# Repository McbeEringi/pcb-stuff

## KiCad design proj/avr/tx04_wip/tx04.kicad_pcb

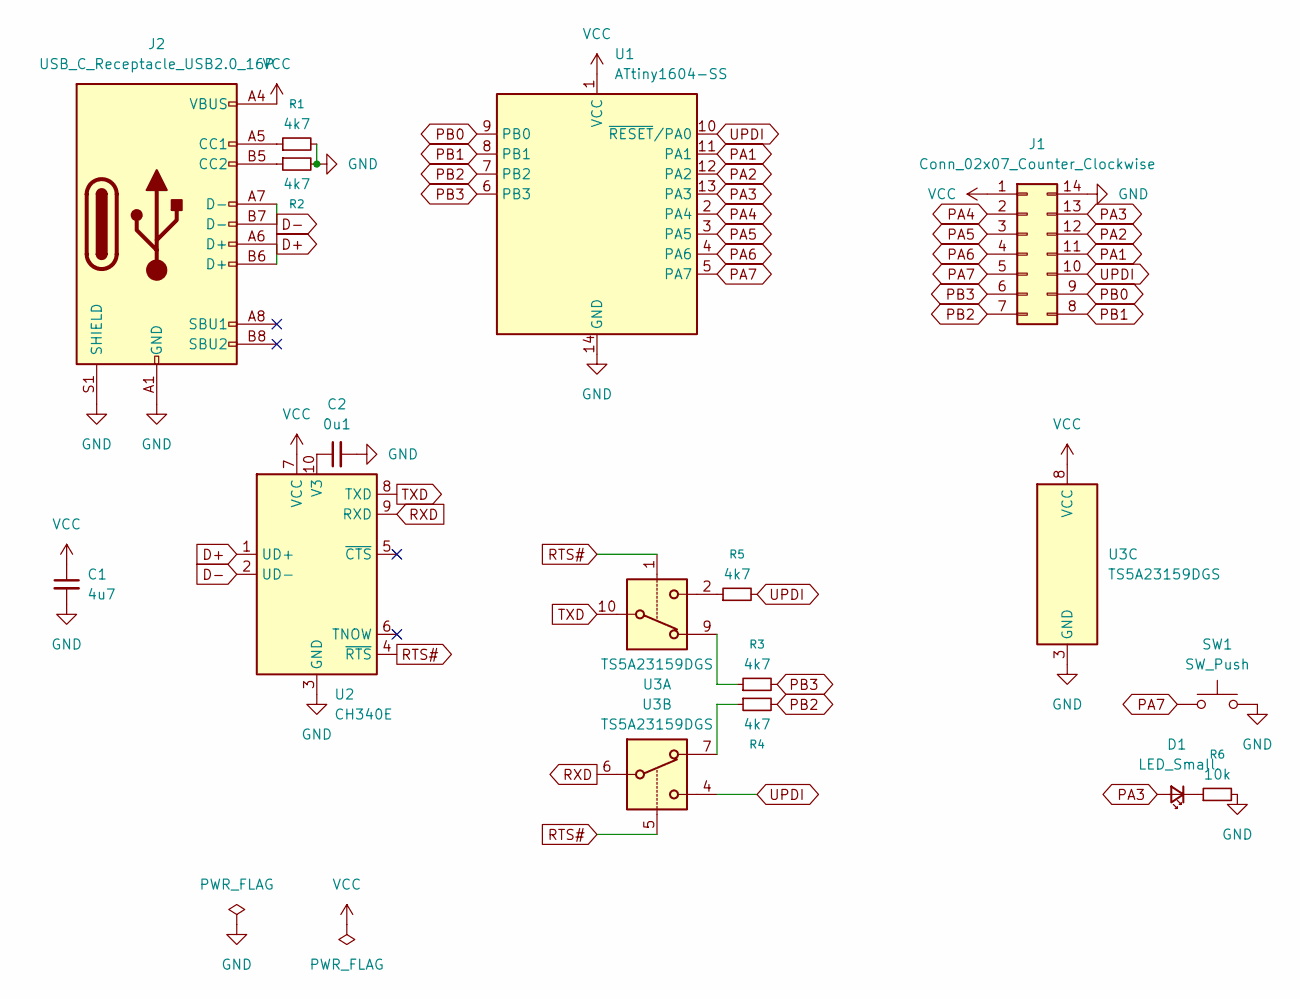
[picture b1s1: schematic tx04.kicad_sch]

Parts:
C1: 4u7; C_0603_1608Metric
C2: 0u1; C_0603_1608Metric
D1: LED_Small; LED_0603_1608Metric
J1: Conn_02x07_Counter_Clockwise; DIP-14_W10.16mm
J2: USB_C_Receptacle_USB2.0_16P; USB_C_Receptacle_GCT_USB4105-xx-A_16P_TopMnt_Horizontal
R1, R2, R3, R4, R5: 4k7; R_0603_1608Metric
R6: 10k; R_0603_1608Metric
SW1: SW_Push; alps-skrp
U1: ATtiny1604-SS; SOIC-14_3.9x8.7mm_P1.27mm
U2: CH340E; MSOP-10_3x3mm_P0.5mm
U3: TS5A23159DGS; VSSOP-10_3x3mm_P0.5mm

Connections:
D+: J2.A6 (D+), J2.B6 (D+), U2.1 (UD+)
D-: J2.A7 (D-), J2.B7 (D-), U2.2 (UD-)
GND: C1.2, C2.2, J1.14, J2.A1 (GND), J2.A12 (GND), J2.B1 (GND), J2.B12 (GND), J2.S1 (SHIELD), R1.2, R2.2, R6.2, SW1.2, U1.14 (GND), U2.3 (GND), U3.3 (GND)
unnamed: D1.1 (K), R6.1
unnamed: J2.A5 (CC1), R1.1
unnamed: J2.B5 (CC2), R2.1
unnamed: R3.1, U3.9
unnamed: R4.1, U3.7
unnamed: R5.1, U3.2
unnamed: C2.1, U2.10 (V3)
PA1: J1.11, U1.11 (PA1)
PA2: J1.12, U1.12 (PA2)
PA3: D1.2 (A), J1.13, U1.13 (PA3)
PA4: J1.2, U1.2 (PA4)
PA5: J1.3, U1.3 (PA5)
PA6: J1.4, U1.4 (PA6)
PA7: J1.5, SW1.1, U1.5 (PA7)
PB0: J1.9, U1.9 (PB0)
PB1: J1.8, U1.8 (PB1)
PB2: J1.7, R4.2, U1.7 (PB2)
PB3: J1.6, R3.2, U1.6 (PB3)
RTS#: U2.4 (~RTS), U3.1, U3.5
RXD: U2.9 (RXD), U3.6
TXD: U2.8 (TXD), U3.10
UPDI: J1.10, R5.2, U1.10 (~RESET/PA0), U3.4
VCC: C1.1, J1.1, J2.A4 (VBUS), J2.A9 (VBUS), J2.B4 (VBUS), J2.B9 (VBUS), U1.1 (VCC), U2.7 (VCC), U3.8 (VCC)

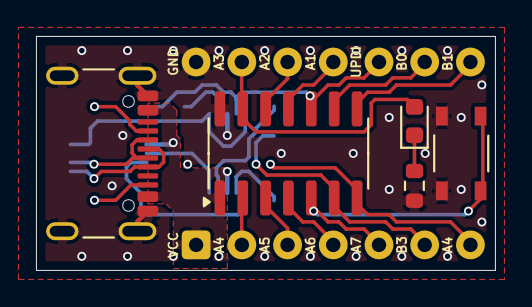
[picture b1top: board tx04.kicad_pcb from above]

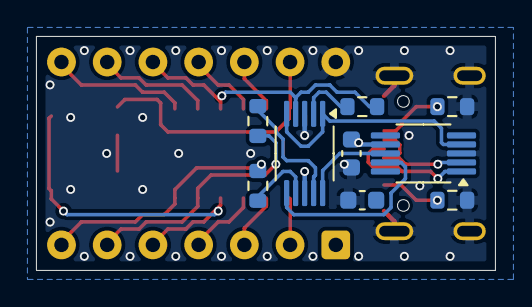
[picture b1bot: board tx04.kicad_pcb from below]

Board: 2 copper layers, 25.5 x 13.0 mm, 15 parts (9 on the bottom side), 26 nets.

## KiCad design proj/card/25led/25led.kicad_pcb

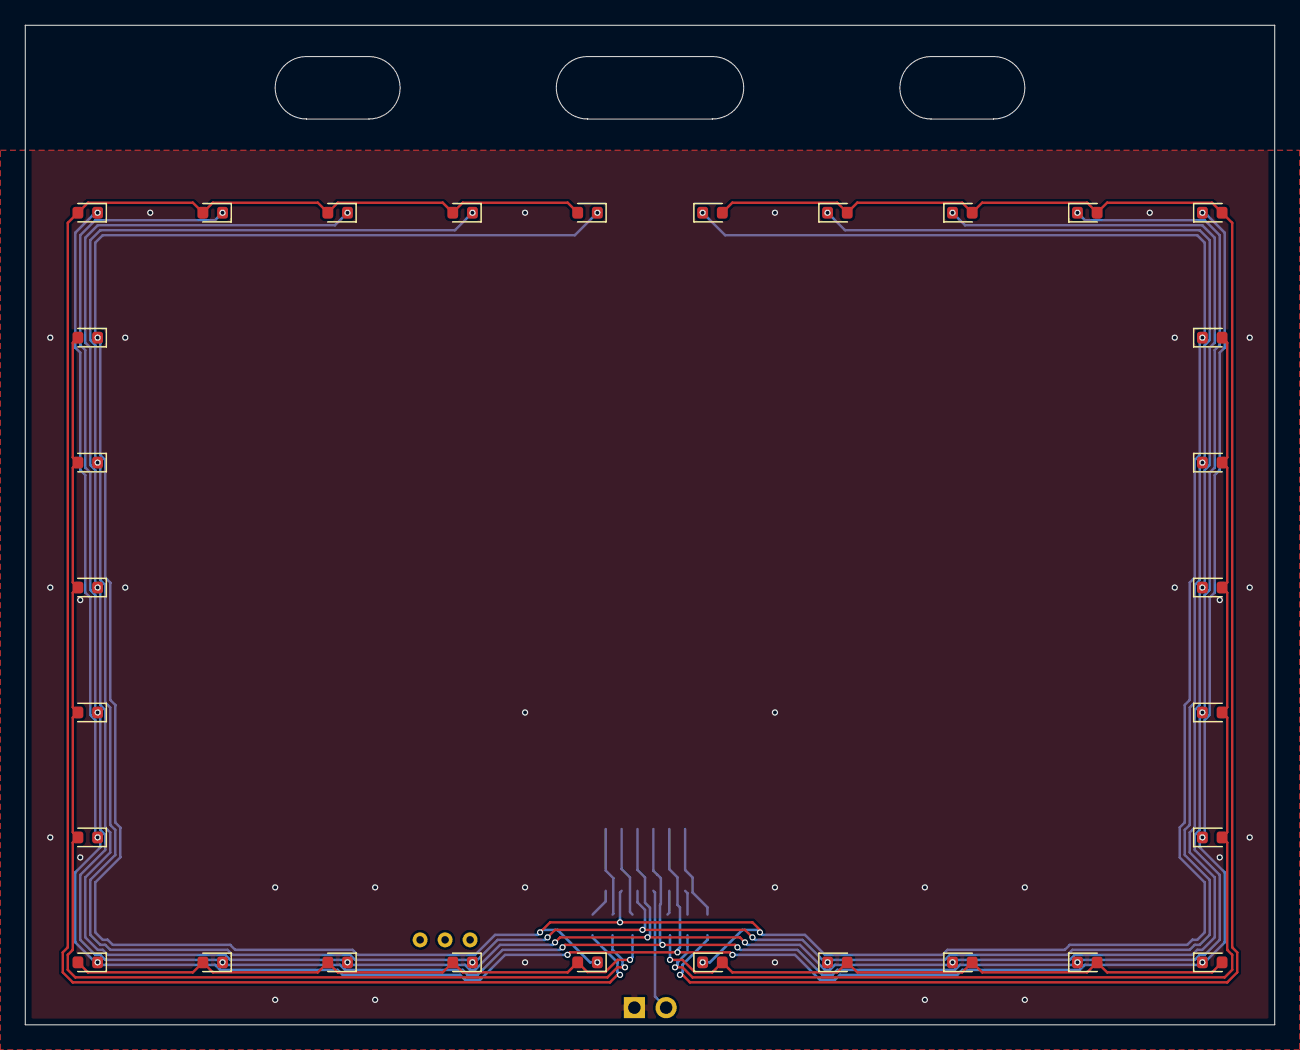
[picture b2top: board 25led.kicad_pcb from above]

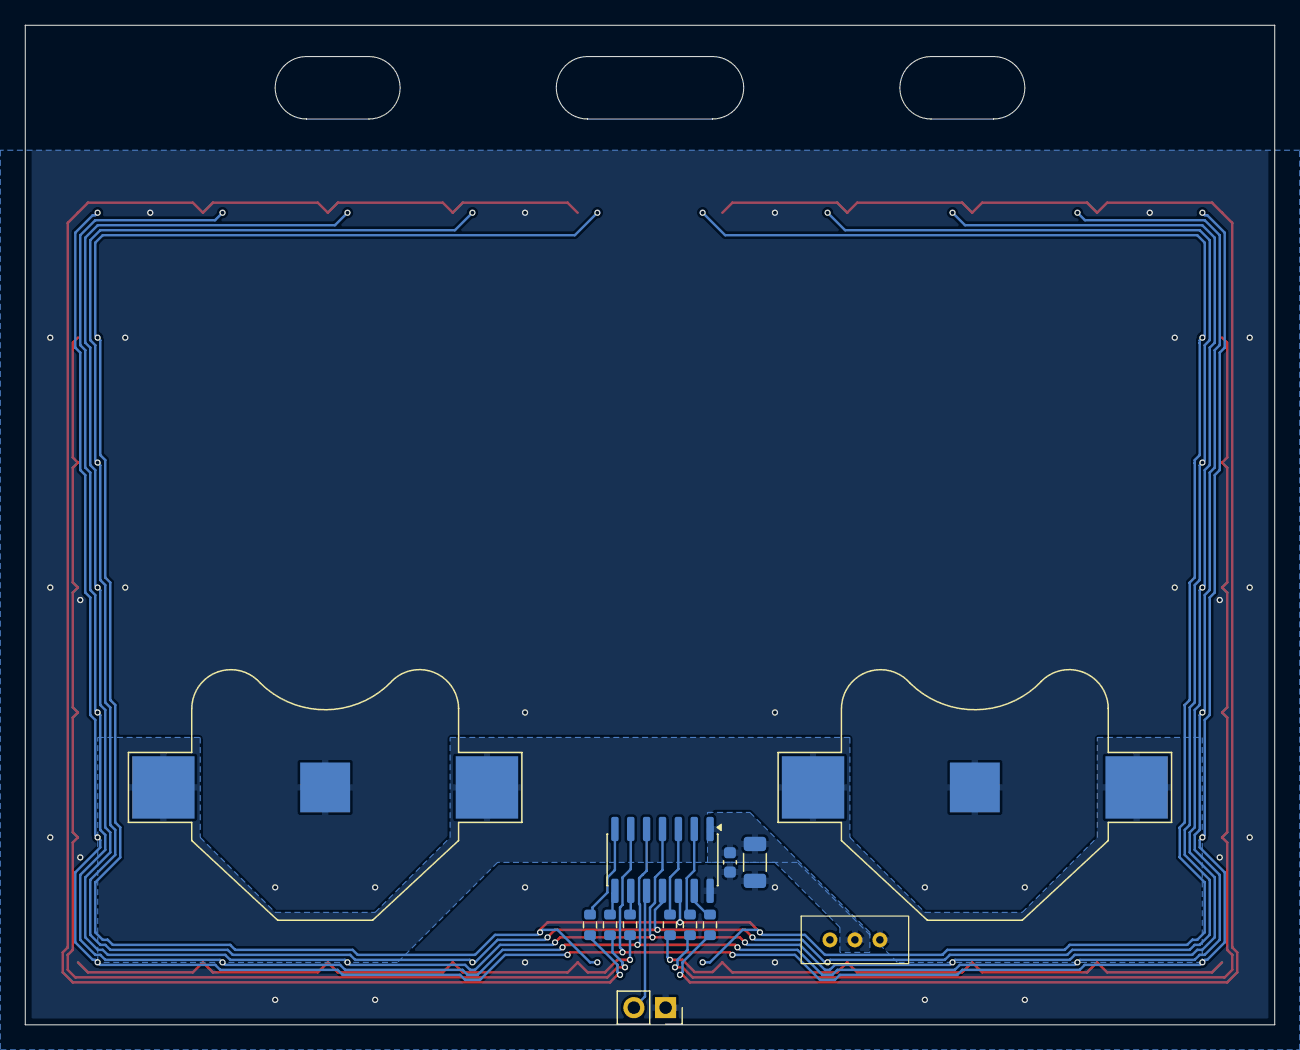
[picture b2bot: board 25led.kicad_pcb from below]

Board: 2 copper layers, 100.0 x 80.0 mm, 43 parts (13 on the bottom side), 21 nets.

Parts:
BT1, BT2: CR2032; BatteryHolder_Multicomp_BC-2001_1x2032
C1: 100u; C_1206_3216Metric
C2: 4u7; C_0603_1608Metric
D1, D2, D3, D4, D5, D6, D7, D8, D9, D10, D11, D12, D13, D14, D15, D16, D17, D18, D19, D20, D21, D22, D23, D24, D25, D26, D27, D28, D29, D30: LED; LED_0603_1608Metric
J1: UPDI; PinSocket_1x02_P2.54mm_Vertical
R1, R2, R3, R4, R5, R6: 100R; R_0603_1608Metric
SW1: SW_SPDT; sw_tht
U1: ATtiny404-SS; SOIC-14_3.9x8.7mm_P1.27mm

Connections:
+BATT: BT1.1 (+), BT2.1 (+), SW1.3 (C)
/_COL1: D1.2 (A), D2.2 (A), D3.2 (A), D4.2 (A), D5.2 (A), R1.2
/_COL2: D6.2 (A), D7.2 (A), D8.2 (A), D9.2 (A), D10.2 (A), R2.2
/_COL3: D11.2 (A), D12.2 (A), D13.2 (A), D14.2 (A), D15.2 (A), R3.2
/_COL4: D16.2 (A), D17.2 (A), D18.2 (A), D19.2 (A), D20.2 (A), R4.2
/_COL5: D21.2 (A), D22.2 (A), D23.2 (A), D24.2 (A), D25.2 (A), R5.2
/_COL6: D26.2 (A), D27.2 (A), D28.2 (A), D29.2 (A), D30.2 (A), R6.2
COL1: R1.1, U1.9 (PB0)
COL2: R2.1, U1.8 (PB1)
COL3: R3.1, U1.7 (PB2)
COL4: R4.1, U1.13 (PA3)
COL5: R5.1, U1.2 (PA4)
COL6: R6.1, U1.3 (PA5)
GND: BT1.2 (-), BT2.2 (-), C1.2, C2.2, J1.1, U1.14 (GND)
ROW1: D1.1 (K), D6.1 (K), D11.1 (K), D16.1 (K), D21.1 (K), D26.1 (K), U1.12 (PA2)
ROW2: D2.1 (K), D7.1 (K), D12.1 (K), D17.1 (K), D22.1 (K), D27.1 (K), U1.11 (PA1)
ROW3: D3.1 (K), D8.1 (K), D13.1 (K), D18.1 (K), D23.1 (K), D28.1 (K), U1.4 (PA6)
ROW4: D4.1 (K), D9.1 (K), D14.1 (K), D19.1 (K), D24.1 (K), D29.1 (K), U1.5 (PA7)
ROW5: D5.1 (K), D10.1 (K), D15.1 (K), D20.1 (K), D25.1 (K), D30.1 (K), U1.6 (PB3)
UPDI: J1.2, U1.10 (~RESET/PA0)
VCC: C1.1, C2.1, SW1.2 (B), U1.1 (VCC)

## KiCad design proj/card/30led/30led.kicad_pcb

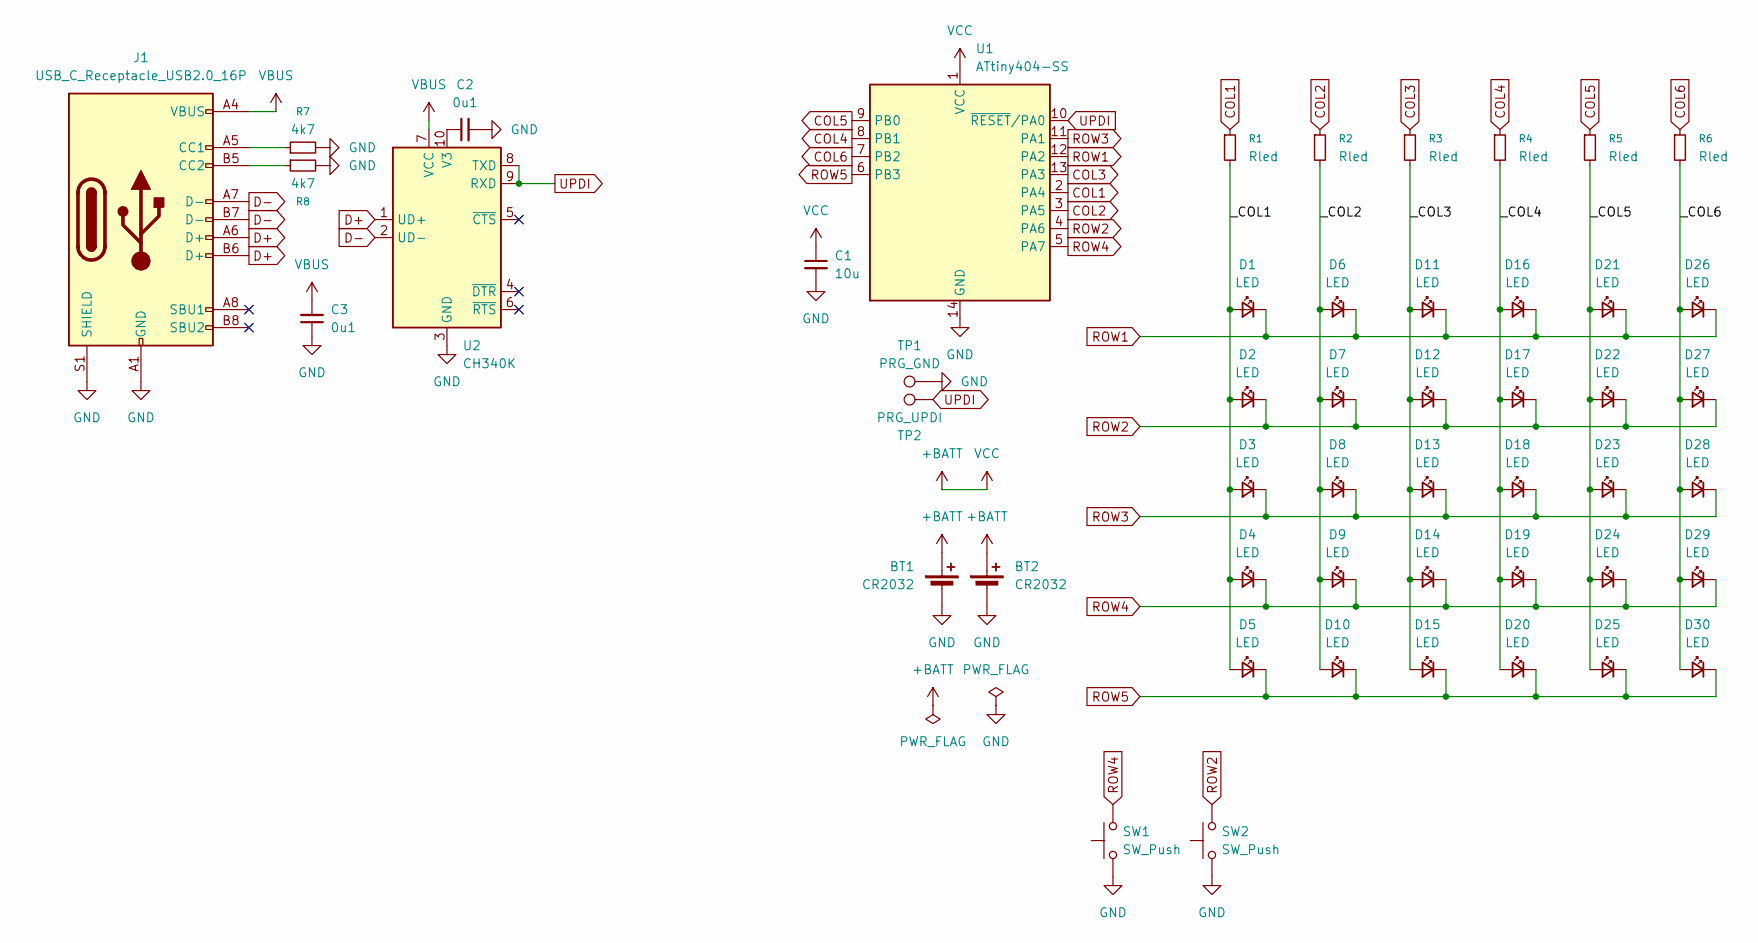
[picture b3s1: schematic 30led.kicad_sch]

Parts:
BT1, BT2: CR2032; BatteryHolder_Multicomp_BC-2001_1x2032
C1: 10u; C_0603_1608Metric
C2, C3: 0u1; C_0603_1608Metric
D1, D2, D3, D4, D5, D6, D7, D8, D9, D10, D11, D12, D13, D14, D15, D16, D17, D18, D19, D20, D21, D22, D23, D24, D25, D26, D27, D28, D29, D30: LED; LED_0603_1608Metric
J1: USB_C_Receptacle_USB2.0_16P; USB_C_Receptacle_GCT_USB4110
R1, R2, R3, R4, R5, R6: Rled; R_0603_1608Metric
R7, R8: 4k7; R_0603_1608Metric
SW1, SW2: SW_Push; alps-skrp
TP1: PRG_GND; TestPoint_Pad_1.5x1.5mm
TP2: PRG_UPDI; TestPoint_Pad_D1.5mm
U1: ATtiny404-SS; SOIC-14_3.9x8.7mm_P1.27mm
U2: CH340K; SSOP-10-1EP_3.9x4.9mm_P1mm_EP2.1x3.3mm

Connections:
+BATT: BT1.1 (+), BT2.1 (+), C1.1, U1.1 (VCC)
/_COL1: D1.2 (A), D2.2 (A), D3.2 (A), D4.2 (A), D5.2 (A), R1.2
/_COL2: D6.2 (A), D7.2 (A), D8.2 (A), D9.2 (A), D10.2 (A), R2.2
/_COL3: D11.2 (A), D12.2 (A), D13.2 (A), D14.2 (A), D15.2 (A), R3.2
/_COL4: D16.2 (A), D17.2 (A), D18.2 (A), D19.2 (A), D20.2 (A), R4.2
/_COL5: D21.2 (A), D22.2 (A), D23.2 (A), D24.2 (A), D25.2 (A), R5.2
/_COL6: D26.2 (A), D27.2 (A), D28.2 (A), D29.2 (A), D30.2 (A), R6.2
COL1: R1.1, U1.2 (PA4)
COL2: R2.1, U1.3 (PA5)
COL3: R3.1, U1.13 (PA3)
COL4: R4.1, U1.8 (PB1)
COL5: R5.1, U1.9 (PB0)
COL6: R6.1, U1.7 (PB2)
D+: J1.A6 (D+), J1.B6 (D+), U2.1 (UD+)
D-: J1.A7 (D-), J1.B7 (D-), U2.2 (UD-)
GND: BT1.2 (-), BT2.2 (-), C1.2, C2.2, C3.1, J1.A1 (GND), J1.A12 (GND), J1.B1 (GND), J1.B12 (GND), J1.S1 (SHIELD), R7.2, R8.2, SW1.1, SW2.1, TP1.1, U1.14 (GND), U2.3 (GND), U2.11 (GND)
unnamed: J1.A5 (CC1), R7.1
unnamed: J1.B5 (CC2), R8.1
unnamed: C2.1, U2.10 (V3)
ROW1: D1.1 (K), D6.1 (K), D11.1 (K), D16.1 (K), D21.1 (K), D26.1 (K), U1.12 (PA2)
ROW2: D2.1 (K), D7.1 (K), D12.1 (K), D17.1 (K), D22.1 (K), D27.1 (K), SW2.2, U1.4 (PA6)
ROW3: D3.1 (K), D8.1 (K), D13.1 (K), D18.1 (K), D23.1 (K), D28.1 (K), U1.11 (PA1)
ROW4: D4.1 (K), D9.1 (K), D14.1 (K), D19.1 (K), D24.1 (K), D29.1 (K), SW1.2, U1.5 (PA7)
ROW5: D5.1 (K), D10.1 (K), D15.1 (K), D20.1 (K), D25.1 (K), D30.1 (K), U1.6 (PB3)
UPDI: TP2.1, U1.10 (~RESET/PA0), U2.8 (TXD), U2.9 (RXD)
VBUS: C3.2, J1.A4 (VBUS), J1.A9 (VBUS), J1.B4 (VBUS), J1.B9 (VBUS), U2.7 (VCC)

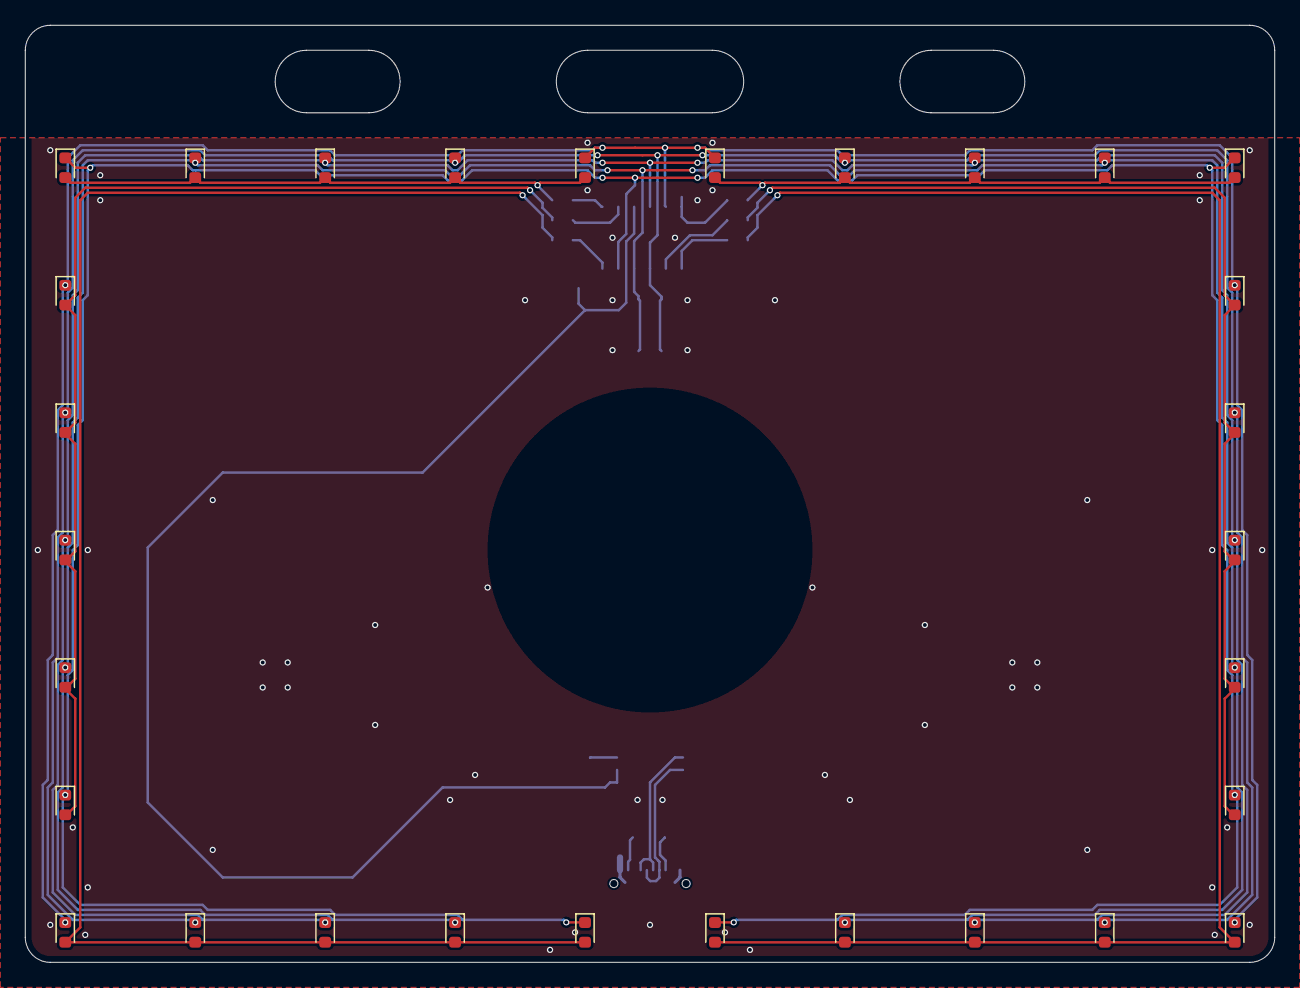
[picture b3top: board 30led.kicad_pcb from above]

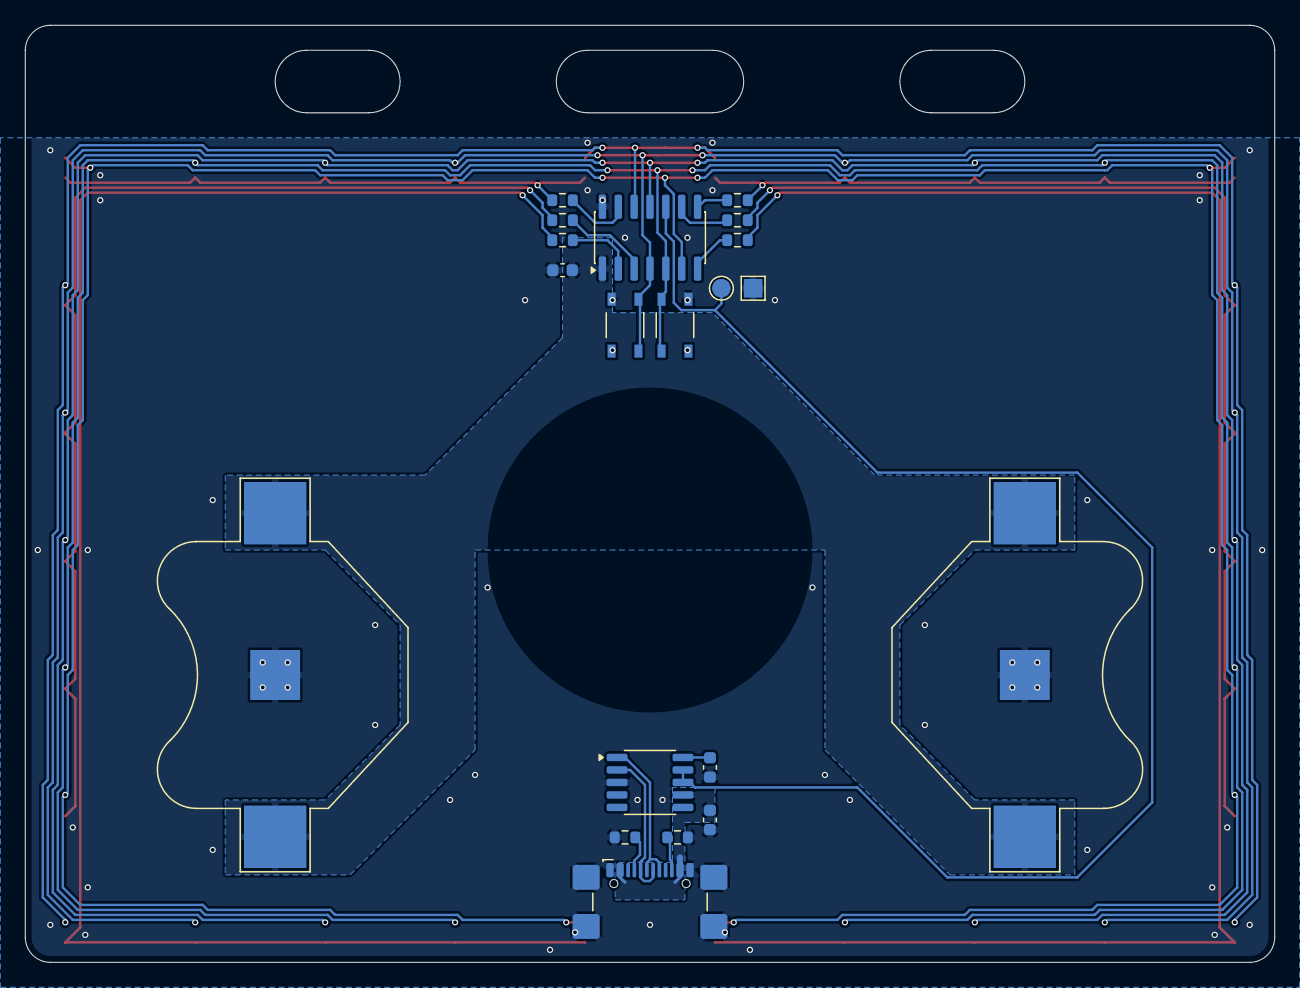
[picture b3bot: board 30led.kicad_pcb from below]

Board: 2 copper layers, 100.0 x 75.0 mm, 50 parts (20 on the bottom side), 26 nets.

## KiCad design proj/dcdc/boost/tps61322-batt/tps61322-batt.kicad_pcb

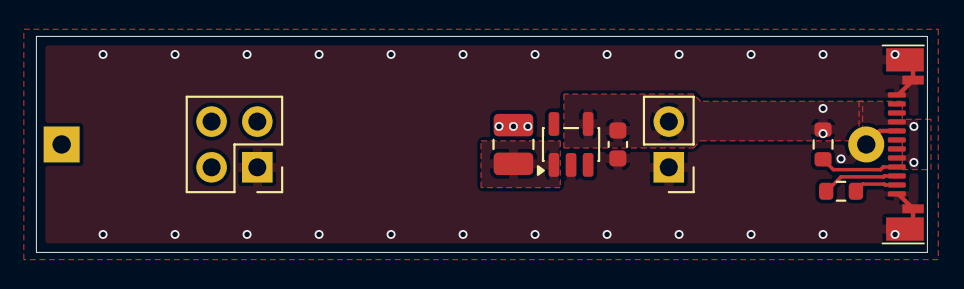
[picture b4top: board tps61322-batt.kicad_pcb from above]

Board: 2 copper layers, 49.5 x 12.0 mm, 9 parts (1 on the bottom side), 7 nets.

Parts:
BT1: Battery_Cell; BatteryHolder_Keystone_2466_1xAAA
C1: 22u; C_0603_1608Metric
J1: Conn_02x02_Odd_Even; PinHeader_2x02_P2.54mm_Vertical
J2: Conn_01x02_Pin; PinHeader_1x02_P2.54mm_Vertical
JP1: BC; R_0603_1608Metric
L1: 4u7; L_1008_2520Metric
P1: USB_C_Plug; USB_C_PLUG_00402-UCAM001-X
R1: 56k; R_0603_1608Metric
U1: TPS613222ADBV; SOT-23-5

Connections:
+5V: C1.1, J2.2, P1.A4 (VBUS), P1.B9 (VBUS), R1.1, U1.4 (VOUT)
+BATT: BT1.1 (+), J1.3, L1.1
GND: BT1.2 (-), C1.2, J1.1, J2.1, P1.A1 (GND), P1.A12 (GND), P1.B12 (GND), P1.S1 (SHIELD), U1.2 (GND)
unnamed: JP1.1 (A), P1.A6 (D+)
unnamed: JP1.2 (B), P1.A7 (D-)
unnamed: P1.A5 (CC), R1.2
unnamed: L1.2, U1.1 (SW)

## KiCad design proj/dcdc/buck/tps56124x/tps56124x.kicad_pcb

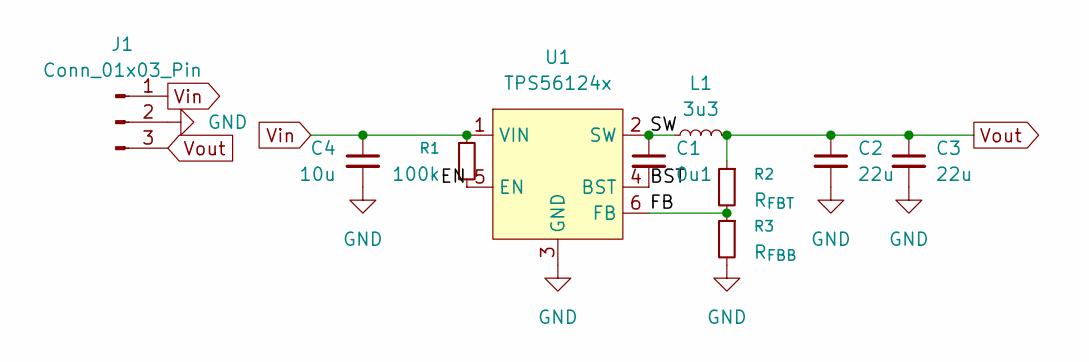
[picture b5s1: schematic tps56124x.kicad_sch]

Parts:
C1: 0u1; C_0603_1608Metric
C2, C3: 22u; C_0603_1608Metric
C4: 10u; C_0603_1608Metric
J1: Conn_01x03_Pin; PinHeader_1x03_P2.54mm_Vertical
L1: 3u3; L_0805_2012Metric
R1: 100k; R_0603_1608Metric
R2: R_{FBT}; R_0603_1608Metric
R3: R_{FBB}; R_0603_1608Metric
U1: TPS56124x; SOT-563

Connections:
/BST: C1.2, U1.4 (BST)
/EN: R1.2, U1.5 (EN)
/FB: R2.2, R3.1, U1.6 (FB)
/SW: C1.1, L1.1, U1.2 (SW)
GND: C2.2, C3.2, C4.2, J1.2, R3.2, U1.3 (GND)
Vin: C4.1, J1.1, R1.1, U1.1 (VIN)
Vout: C2.1, C3.1, J1.3, L1.2, R2.1

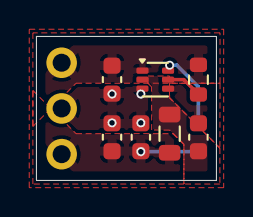
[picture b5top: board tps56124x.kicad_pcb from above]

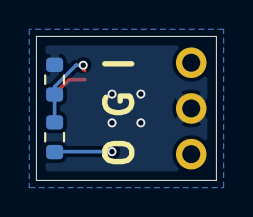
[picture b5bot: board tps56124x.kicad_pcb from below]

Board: 2 copper layers, 10.0 x 8.0 mm, 10 parts (3 on the bottom side), 7 nets.

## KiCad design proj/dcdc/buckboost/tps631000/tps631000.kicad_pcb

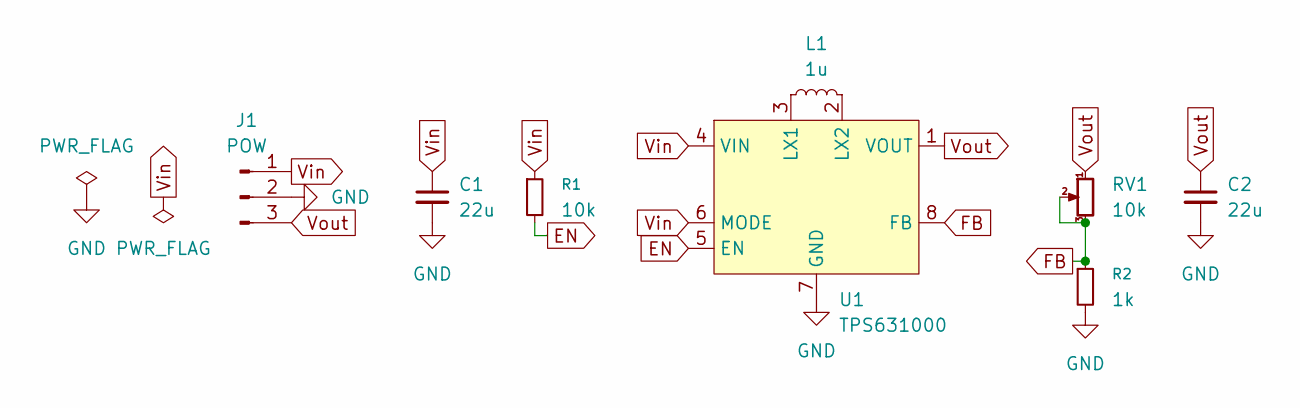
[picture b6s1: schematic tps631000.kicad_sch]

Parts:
C1, C2: 22u; C_0603_1608Metric
J1: POW; PinHeader_1x03_P2.54mm_Vertical
L1: 1u; L_1008_2520Metric
R1: 10k; R_0603_1608Metric
R2: 1k; R_0603_1608Metric
RV1: 10k; TSR-C3305
U1: TPS631000; SOT-583-8

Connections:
EN: R1.2, U1.5 (EN)
FB: R2.1, RV1.2, RV1.3, U1.8 (FB)
GND: C1.2, C2.2, J1.2, R2.2, U1.7 (GND)
unnamed: L1.1, U1.3 (LX1)
unnamed: L1.2, U1.2 (LX2)
Vin: C1.1, J1.1, R1.1, U1.4 (VIN), U1.6 (MODE)
Vout: C2.1, J1.3, RV1.1, U1.1 (VOUT)

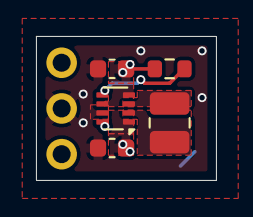
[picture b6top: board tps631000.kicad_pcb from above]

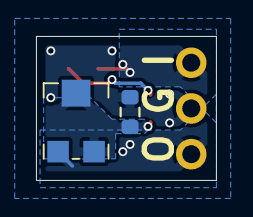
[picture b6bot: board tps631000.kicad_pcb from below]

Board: 2 copper layers, 10.0 x 8.0 mm, 8 parts (3 on the bottom side), 7 nets.
